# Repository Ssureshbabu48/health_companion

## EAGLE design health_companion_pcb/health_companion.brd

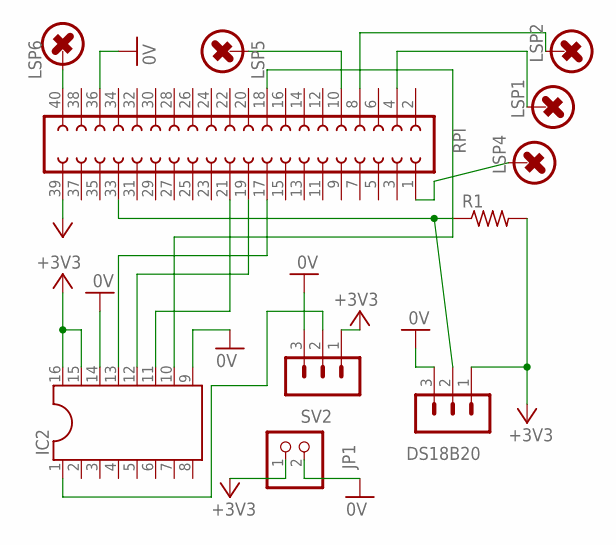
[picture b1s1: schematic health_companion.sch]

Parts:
DS18B20: MA03-1
IC2: DIL16
JP1: PINHD-1X2; 1X02
LSP1, LSP2, LSP4, LSP5, LSP6: LSP11-VAR12.8MM; LSP11
R1: R-US_0204/5; 0204/5
RPI: FE20-2
SV2: MA03-1

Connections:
0V: DS18B20.3, IC2.9, IC2.14, JP1.2, RPI.36, SV2.3
+3V3: DS18B20.1, IC2.15, IC2.16, JP1.1, R1.2, RPI.39, SV2.1
unnamed: IC2.10, RPI.18
unnamed: DS18B20.2, R1.1, RPI.33
unnamed: IC2.13, RPI.17
unnamed: IC2.12, RPI.19
unnamed: IC2.11, RPI.21
unnamed: IC2.1, SV2.2
unnamed: LSP2.MP, RPI.8
unnamed: LSP1.MP, RPI.4
unnamed: LSP6.MP, RPI.40
unnamed: LSP4.MP, RPI.1
unnamed: LSP5.MP, RPI.10

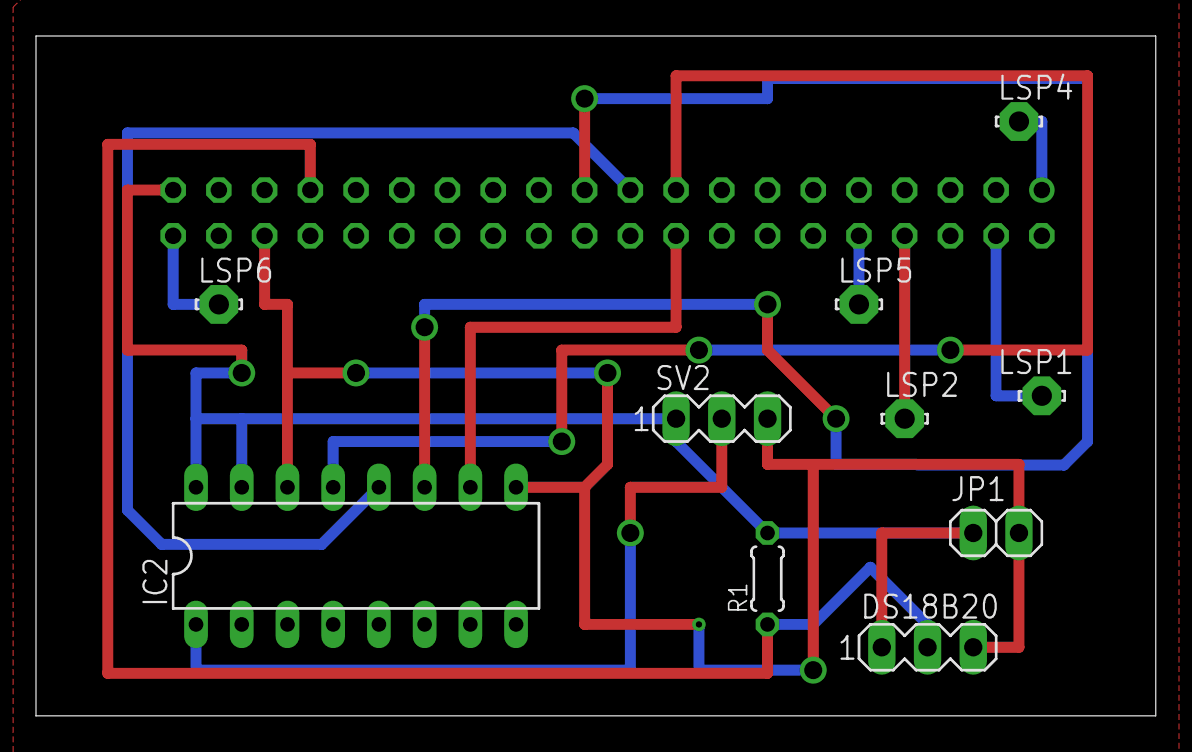
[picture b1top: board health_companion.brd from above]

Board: 2 copper layers, 62.2 x 37.8 mm, 11 parts (1 on the bottom side), 13 nets.

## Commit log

2019-05-08 Updated PCB Design
2019-05-08 Removed hello world
2022-02-14 Bump follow-redirects from 1.7.0 to 1.14.8 in /health_companion_backend
    Bumps [follow-redirects](https://github.com/follow-redirects/follow-redirects) from 1.7.0 to 1.14.8.
    - [Release notes](https://github.com/follow-redirects/follow-redirects/releases)
    - [Commits](https://github.com/follow-redirects/follow-redirects/compare/v1.7.0...v1.14.8)
    ---
    updated-dependencies:
    - dependency-name: follow-redirects
